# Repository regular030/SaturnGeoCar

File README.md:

# NON-PERSONAL OR EDUCATION USE OF THIS PROJECT IS PROHIBITED, USERS WILL BE PROSECUTED! 
# SaturnGeoCar

The project is done in EasyEDA

More info to be coming

Price So far: $374.57 with shipping and taxes and PCBA

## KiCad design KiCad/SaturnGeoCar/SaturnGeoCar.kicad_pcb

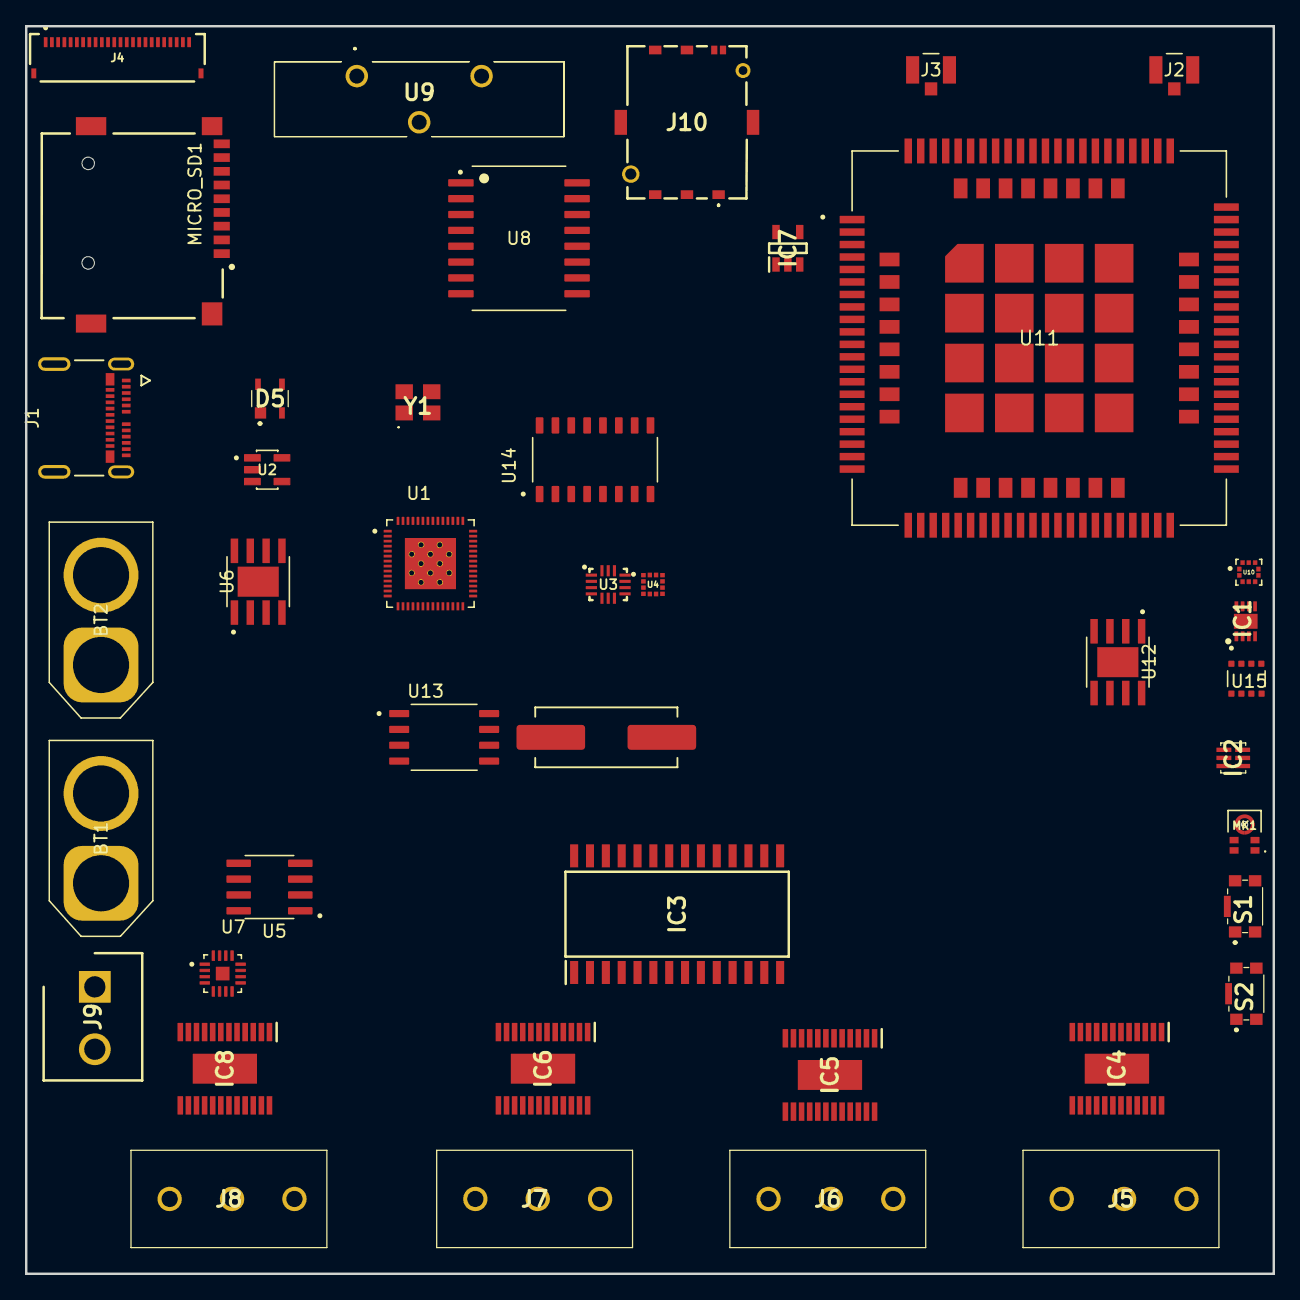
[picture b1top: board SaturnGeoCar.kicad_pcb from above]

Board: 2 copper layers, 100.0 x 100.0 mm, 42 parts (0 on the bottom side), 74 nets, no tracks yet.

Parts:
BT1, BT2: XT60-F; AMASS_XT60-F_1x02_P7.20mm_Vertical
D5: TPD2E001DZDR
IC1: SHT31-DIS-B2.5KS; SON50P250X250X100-9N-D
IC2: TSL25911FN
IC3: MCP23017-E_SO; SOIC127P1030X265-28N
IC4, IC5, IC6, IC8: DRV10983PWPR; SOP65P640X120-25N
IC7: AP2112K-1.8TRG1; SOT95P285X140-5N
J1: 1054500101; MOLEX_1054500101
J2, J3: U.FL-R-SMT-1_80_; HIROSE_U.FL-R-SMT-1_80_
J4: FFC2B28-24-G; GCT_FFC2B28-24-G
J5, J6, J7, J8: WJ126V-5.0-3P; WJ126V503P
J9: WJ126V-5.0-2P; SHDR2W105P0X500_1X2_1000X780X1040P
J10: SIM8055-6-1-14-01-A; SIM8055611401A
MICRO_SD1: TF-01A
MK1: SPH0641LU4H-1; MIC_SPH0641LU4H-1
S1, S2: KMR221GLFS; KMR231GLFS
U1: ESP32-S3; IC_ESP32-S3
U2: AP2112K-3.3TRG1; SOT95P285X140-5N
U3: LSM6DS3TR-C; LGA-14-2.5X3MM
U4: LIS3MDLTR; XDCR_LIS3MDLTR
U5: INA219AID; SOIC127P599X175-8N
U6, U12: MP1584EN-LF-Z; SOIC127P600X170-9N
U7: MAX98357AETE_T; QFN50P300X300X80-17N
U8: DS3231SN_T_R; SOIC127P1032X265-16N
U9: CR2032-BS-5-1; CR2032BS51
U10: BMP388; PQFN50P200X200X80-10N
U11: SIM7600G; IC_SIM7600G
U13: W25Q128JVSIQ; SOIC127P790X216-8N
U14: CH340C; SOIC127P600X180-16N
U15: BME680; PSON80P300X300X100-8N
X1: X321532768KGD2SI; CRYSTAL-SMD_L11.5-W4.8-LS12.7
Y1: X322540MPB4SI

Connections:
+3V3: IC1.5 (VDD), IC1.6 (NRESET), IC2.5 (VDD), IC3.9 (VDD), J4.1, J4.2, J4.3, MICRO_SD1.4 (VDD), MK1.5 (VDD), U1.2 (VDD3P3), U1.3 (VDD3P3), U1.20 (VDD3P3_RTC), U1.29 (VDD_SPI), U1.46 (VDD3P3_CPU), U1.55 (VDDA1), U1.56 (VDDA2), U3.5 (VDDIO), U3.8 (VDD), U3.12 (CS), U4.5 (VDD), U4.6 (VDD_IO), U4.10 (CS), U5.5 (VS), U7.7 (VDD), U7.8 (VDD), U8.2 (VCC), U10.1 (VDDIO), U10.6 (CSB), U10.10 (VDD), U13.8 (VCC), U14.16 (VCC), U15.2 (CSB), U15.6 (VDDIO), U15.8 (VDD)
+5V: IC7.1 (VIN), IC7.3 (EN), J1.A4 (VBUS_A4), J1.A9 (VBUS_A9), J1.B4 (VBUS_B4), J1.B9 (VBUS_B9), U2.1 (VIN), U2.3 (EN), U11.11 (USB_VBUS)
+11.1V: BT1.1 (+), BT2.1 (+), IC4.23 (VCC_1), IC4.24 (VCC_2), IC5.23 (VCC_1), IC5.24 (VCC_2), IC6.23 (VCC_1), IC6.24 (VCC_2), IC8.23 (VCC_1), IC8.24 (VCC_2), U5.7 (VIN-), U6.7 (VIN), U12.7 (VIN)
BCLK: MK1.4 (CLOCK), U1.11 (GPIO6), U7.16 (BCLK)
CAMPCLK: J4.22, U1.45 (MTDO)
CAMPWDN: J4.11, U1.8 (GPIO3)
CAMXCLK: J4.10, J4.23, U1.44 (MTCK)
COM1: IC3.6 (GPB5), S2.1 (COM_1)
CardDetect: IC3.5 (GPB4), MICRO_SD1.CD1 (CD)
D0: J4.14, U1.52 (GPIO46)
D1: J4.15, U1.39 (GPIO34)
D2: J4.16, U1.40 (GPIO35)
D3: J4.17, U1.41 (GPIO36)
D4: J4.18, U1.38 (GPIO33)
D5: J4.19, U1.5 (GPIO0)
D6: J4.20, U1.48 (MTMS)
D7: J4.21, U1.47 (MTDI)
D+: D5.2 (IO1), J1.A6 (D1+), J1.B6 (D2+), U1.27 (GPIO21), U11.13 (USB_DP), U14.5 (UD+)
D-: D5.3 (IO2), J1.A7 (D1-), J1.B7 (D2-), U1.26 (GPIO20), U11.12 (USB_DN), U14.6 (UD-)
DATA: MK1.1 (DATA), U1.51 (GPIO45)
DIN: U1.13 (GPIO8), U7.1 (DIN)
DIR1: IC3.1 (GPB0), IC4.14 (DIR)
DIR2: IC3.2 (GPB1), IC5.14 (DIR)
DIR3: IC3.3 (GPB2), IC6.14 (DIR)
DIR4: IC3.4 (GPB3), IC8.14 (DIR)
FCLK: U1.33 (SPICLK), U1.37 (SPICLK_P), U13.6 (CLK)
FCS: U1.32 (SPICS0), U13.1 (/CS)
FIO0: U1.34 (SPIQ), U13.5 (DI(IO0))
FIO1: U1.35 (SPID), U13.2 (DO(IO1))
FIO2: U1.31 (SPIWP), U13.3 (/WP(IO2))
FIO3: U1.30 (SPIHD), U13.7 (/HOLD/RESET(IO3))
GND: BT1.2 (-), BT2.2 (-), D5.1 (GND), IC1.2 (ADDR), IC1.8 (VSS), IC1.9 (EP), IC2.3 (GND), IC3.10 (VSS), IC3.15 (A0), IC3.16 (A1), IC3.17 (A2), IC4.5 (SWGND), IC4.8 (GND), IC4.15 (PGND_1), IC4.16 (PGND_2), IC4.25 (THERMAL_PAD_(GND)), IC5.5 (SWGND), IC5.8 (GND), IC5.15 (PGND_1), IC5.16 (PGND_2), IC5.25 (THERMAL_PAD_(GND)), IC6.5 (SWGND), IC6.8 (GND), IC6.15 (PGND_1), IC6.16 (PGND_2), IC6.25 (THERMAL_PAD_(GND)), IC7.2 (GND), IC8.5 (SWGND), IC8.8 (GND), IC8.15 (PGND_1), IC8.16 (PGND_2), IC8.25 (THERMAL_PAD_(GND)), J1.A1 (GND_A1), J1.A12 (GND_A12), J1.B1 (GND_B1), J1.B12 (GND_B12), J1.SH1 (SHIELD3), J1.SH2 (SHIELD4), J1.SH3 (SHIELD1), J1.SH4 (SHIELD2), J2.G1, J2.G2, J3.G1, J3.G2, J4.4, J4.5, J4.8, J4.24, J4.S1 (SHIELD), J4.S2 (SHIELD), J10.C5 (GND), J10.MH1, J10.MH2, J10.MP1, J10.MP2, MICRO_SD1.6 (VSS), MICRO_SD1.MP1 (SHIELD), MICRO_SD1.MP2 (SHIELD), MICRO_SD1.MP3 (SHIELD), MICRO_SD1.MP4 (SHIELD), MK1.2 (SELECT), MK1.3 (GND), S1.2 (NO_1), S1.5 (GND), S2.2 (NO_1), S2.5 (GND), U1.57 (GND), U2.2 (GND), U3.1 (SDO/SA0), U3.6 (GND), U3.7 (GND), U4.2 (RSVD1), U4.3 (GND), U4.9 (SDO/SA1), U4.12 (RSVD2), U5.1 (A1), U5.2 (A0), U5.6 (GND), U5.8 (VIN+), U6.5 (GND), U6.9 (EP), U7.2 (GAIN_SLOT), U7.3 (GND), U7.4 (SD_MODE), U7.11 (GND), U7.15 (GND), U7.17 (EP), U8.13 (GND), U9.3 (-), U10.3 (VSS), U10.5 (SDO), U10.8 (VSS), U10.9 (VSS), U11.1 (GND), U11.2 (GND), U11.5 (GND), U11.10 (GND), U11.14 (GND), U11.37 (GND), U11.40 (GND), U11.41 (GND), U11.43 (GND), U11.57 (GND), U11.58 (GND), U11.60 (GND), U11.61 (GND), U11.64 (GND), U11.65 (GND), U11.77 (GND), U11.78 (GND), U11.80 (GND), U11.81 (GND), U11.83 (COEX1), U11.84 (COEX2), U11.86 (COEX3), U11.93 (GND), U11.98 (GND), U11.110 (GND), U11.118 (GND), U11.120 (GND), U11.121 (GND), U11.122 (GND), U11.123 (GND), U11.124 (GND), U11.125 (GND), U11.126 (GND), U11.127 (GND), U11.128 (GND), U11.129 (GND), U11.130 (GND), U11.131 (GND), U11.132 (GND), U11.133 (GND), U11.134 (GND), U11.135 (GND), U12.5 (GND), U12.9 (EP), U13.4 (GND), U14.1 (GND), U15.1 (GND), U15.5 (SDO), U15.7 (GND), Y1.2 (GND_1), Y1.4 (GND_2)
GNSSA: J3.SIG, U11.79 (GNSS_ANT)
LRCLK: U1.12 (GPIO7), U7.14 (LRCLK)
LTEA: J2.SIG, U11.82 (MAIN_ANT)
NS: J9.2, U7.10 (OUTN)
unnamed: U11.38 (VBAT), U11.39 (VBAT), U11.62 (VBAT), U11.63 (VBAT)
unnamed: U1.22 (XTAL_32K_N), X1.2
unnamed: U1.21 (XTAL_32K_P), X1.1
unnamed: U1.53 (XTAL_N), Y1.3 (CRYSTAL_2)
unnamed: U1.54 (XTAL_P), Y1.1 (CRYSTAL_1)
unnamed: U8.14 (VBAT), U9.1 (+_1), U9.2 (+_2)
PS: J9.1, U7.9 (OUTP)
PWRKEY: U1.14 (GPIO9), U11.3 (~PWRKEY)
RESET: IC3.18 (~RESET), J4.9, S1.1 (COM_1), U1.4 (CHIP_PU), U1.43 (GPIO38), U11.4 (~RESET)
SCL: IC1.4 (SCL), IC2.1 (SCL), IC3.12 (SCL), IC4.10 (SCL), IC5.10 (SCL), IC6.10 (SCL), IC8.10 (SCL), J4.7, U1.9 (GPIO4), U3.13 (SCL), U4.1 (SCL/SPC), U5.4 (SCL), U8.16 (SCL), U10.2 (SCK), U11.55 (SCL), U15.4 (SCK)
SDA: IC1.1 (SDA), IC2.6 (SDA), IC3.13 (SDA), IC4.11 (SDA), IC5.11 (SDA), IC6.11 (SDA), IC8.11 (SDA), J4.6, U1.10 (GPIO5), U3.14 (SDA), U4.11 (SDA/SDI/SDO), U5.3 (SDA), U8.15 (SDA), U10.4 (SDI), U11.56 (SDA), U15.3 (SDI)
SDCLK: MICRO_SD1.5 (CLK), U1.24 (GPIO18)
SDCMD: MICRO_SD1.3 (CMD), U1.19 (GPIO14)
SDDAT0: MICRO_SD1.7 (DAT0), U1.23 (GPIO17)
SDDAT3: MICRO_SD1.2 (CD/DAT3), U1.25 (GPIO19)
SIMCD: J10.CD1 (CD), U11.53 (USIM_DET)
SIMCLK: J10.C3 (CLK), U11.19 (USIM_CLK)
SIMDATA: J10.C7 (I/O), U11.17 (USIM_DATA)
SIMRESET: J10.C2 (RST), U11.18 (USIM_RST)
SIMVCC: J10.C1 (VCC), U11.20 (USIM_VDD)
SPEED1: IC4.13 (SPEED), U1.18 (GPIO13)
SPEED2: IC5.13 (SPEED), U1.17 (GPIO12)
SPEED3: IC6.13 (SPEED), U1.16 (GPIO11)
SPEED4: IC8.13 (SPEED), U1.15 (GPIO10)
U1: IC4.17 (U_1), IC4.18 (U_2), J5.1
U2: IC5.17 (U_1), IC5.18 (U_2), J6.1
U3: IC6.17 (U_1), IC6.18 (U_2), J7.1
U4: IC8.17 (U_1), IC8.18 (U_2), J8.1
V1: IC4.19 (V_1), IC4.20 (V_2), J5.2
V2: IC5.19 (V_1), IC5.20 (V_2), J6.2
V3: IC6.19 (V_1), IC6.20 (V_2), J7.2
V4: IC8.19 (V_1), IC8.20 (V_2), J8.2
W1: IC4.21 (W_1), IC4.22 (W_2), J5.3
W2: IC5.21 (W_1), IC5.22 (W_2), J6.3
W3: IC6.21 (W_1), IC6.22 (W_2), J7.3
W4: IC8.21 (W_1), IC8.22 (W_2), J8.3
uC_RX: U1.7 (GPIO2), U1.50 (U0RXD), U11.68 (RXD), U14.3 (RXD)
uC_TX: U1.6 (GPIO1), U1.49 (U0TXD), U11.71 (TXD), U14.2 (TXD)

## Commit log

2025-06-26 uploaded kicad files
2025-06-29 added some components, detailed list tba
2025-06-30 Finished uploading all components, wiring has started
2025-06-30 updated a few parts
2025-07-01 Create LICENSE
2025-07-08 finshed adding all componets, everything is wired properly. Adding solar panel next
2025-08-15 hehe easyeda sucks (almost done)
2025-08-16 pcb stuff idk ima kms
2025-08-16 everything has been placed, wiring next
2025-08-16 breakout board fully done, costs around 100usd for 2 LOL
2025-08-21 Finished PCB, fuck EasyEDA, Will be reviewed later
2025-08-21 reorg
2025-08-21 Update LICENSE
